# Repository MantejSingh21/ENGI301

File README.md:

# <h1> ENGI301 Project 1 + 2 
# <h1> Bubba the Spider Robot

This is the repository that contains information on building Bubba the spider robot.It contains the code repo.
The full length build and operation instructions are located in the hackster page: 

  https://www.hackster.io/ms146/bubba-the-quadrupedal-spider-robot-7b09ac

 <12/03/21>
This repo also contains the gerber, brd and schem files required to print the custom circuit board. It also contains the bill of materials for all the required part.
   
This is found in project_02/docs.
  
Repository for ENGI301 course work.

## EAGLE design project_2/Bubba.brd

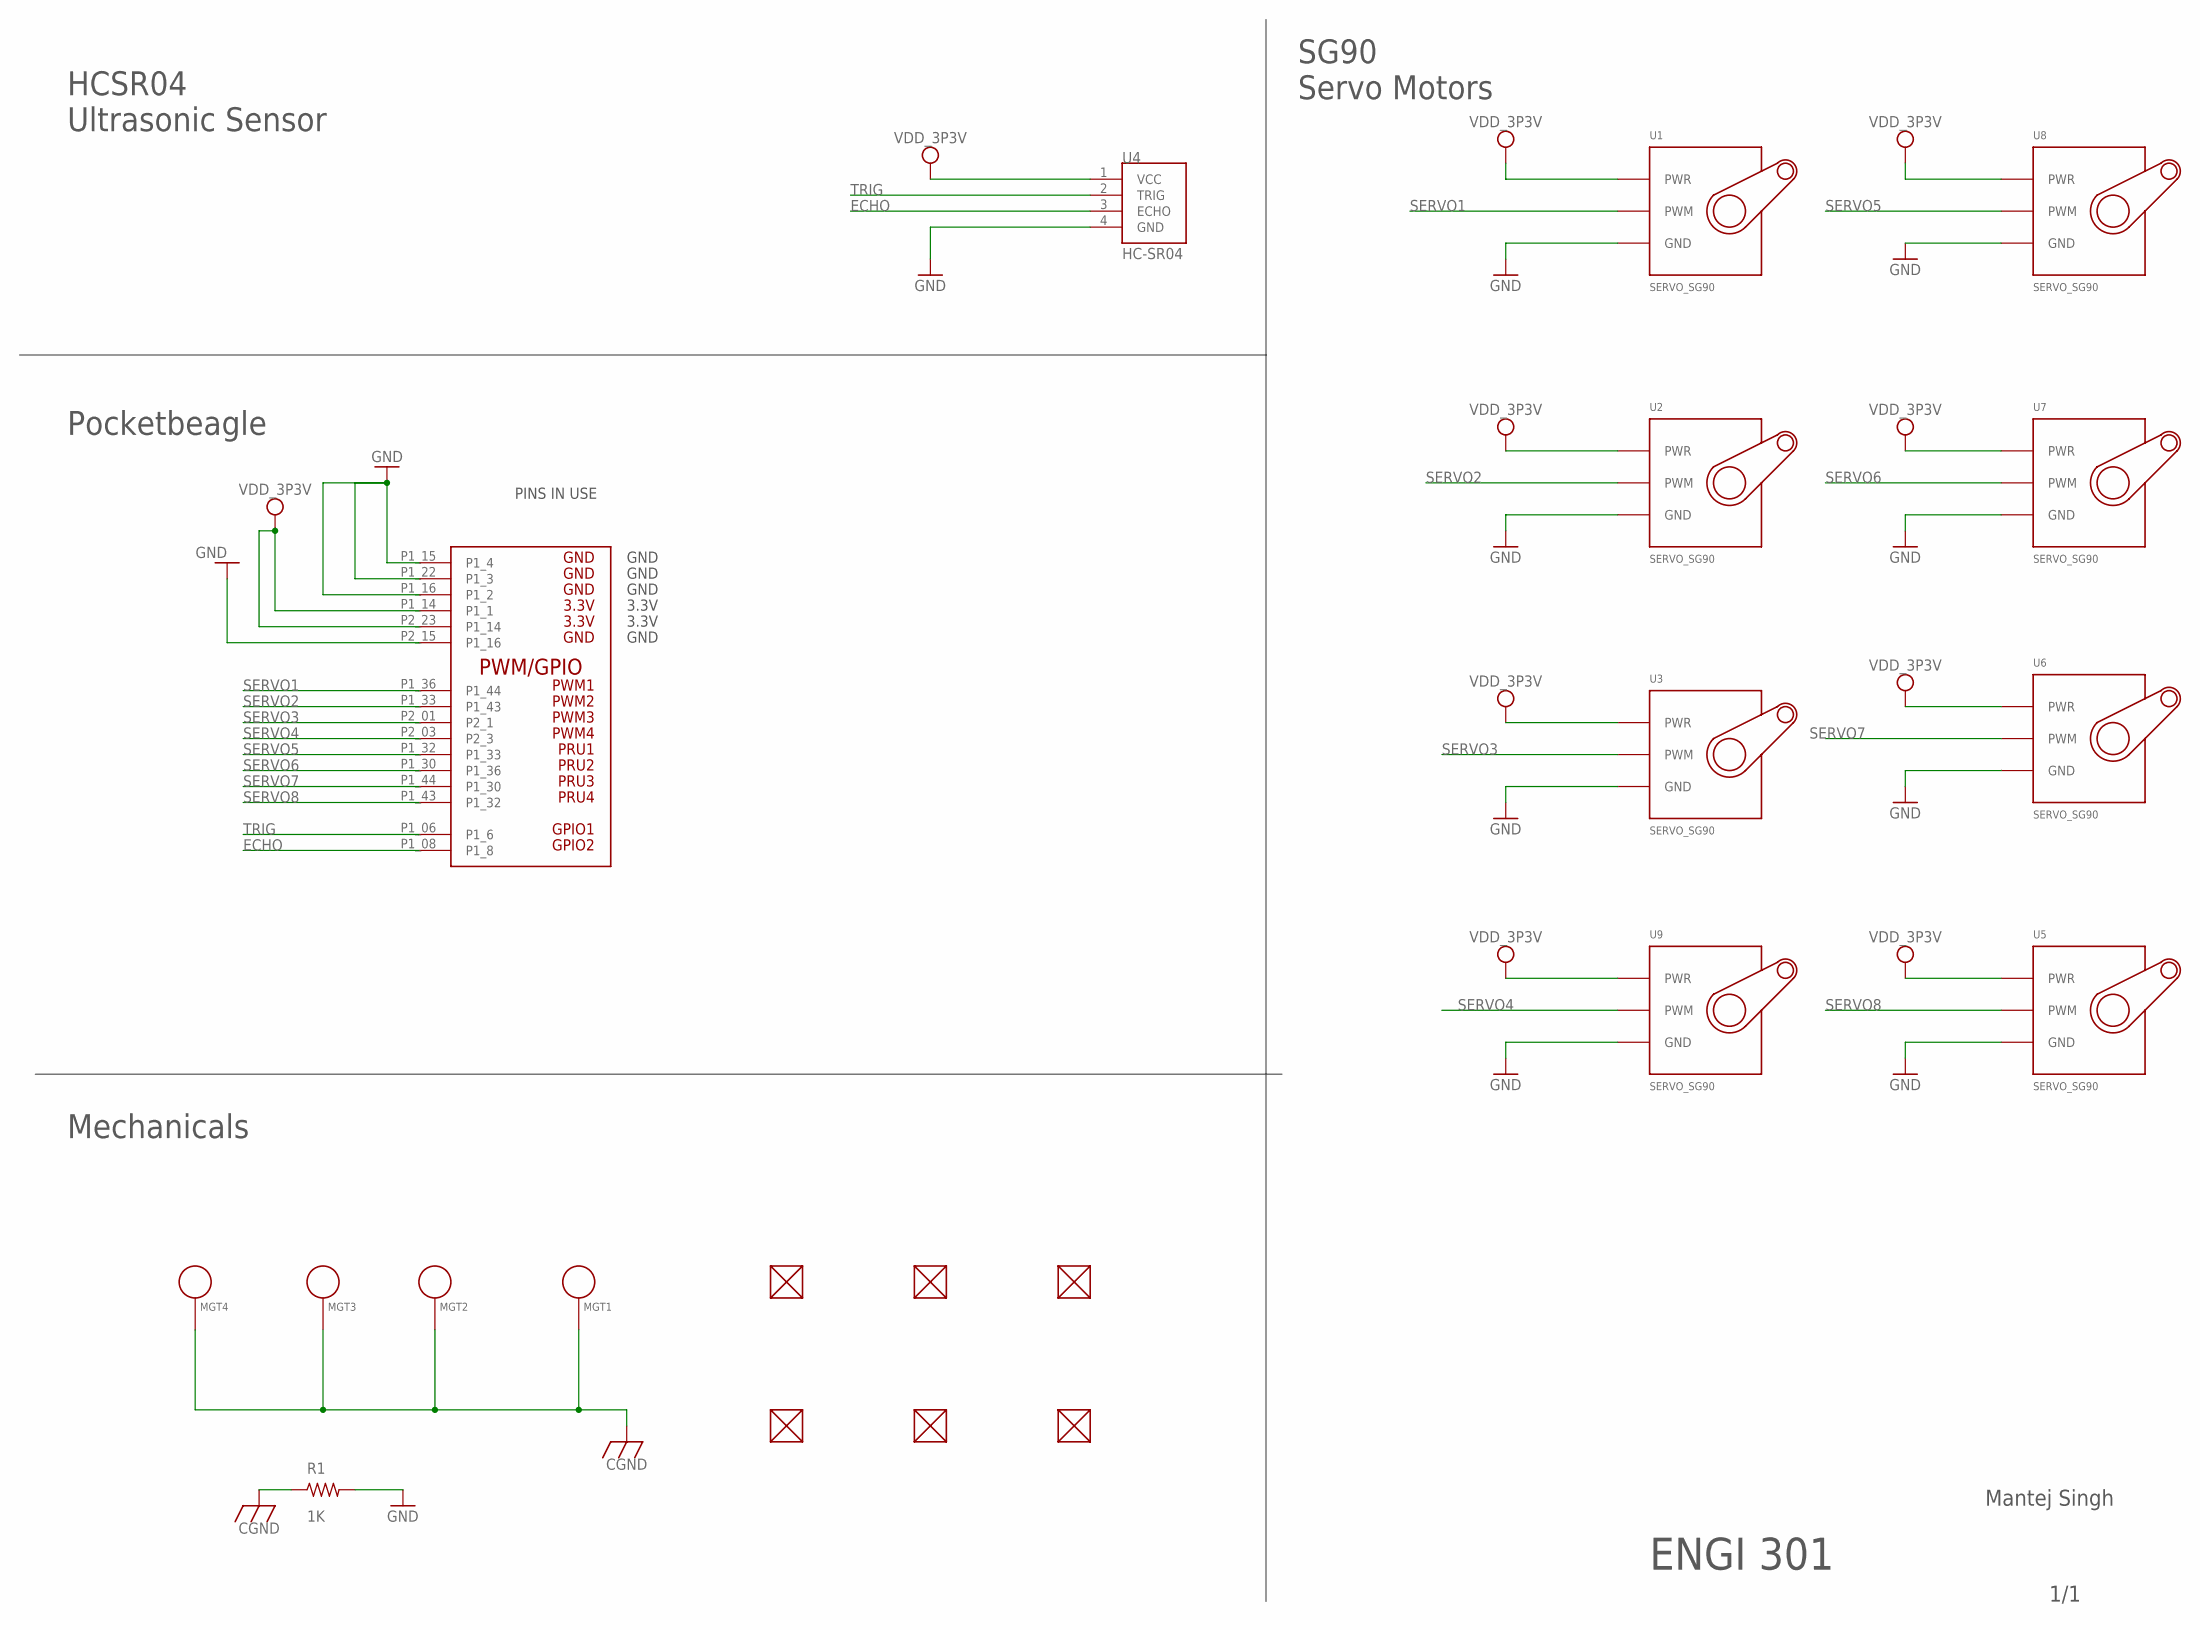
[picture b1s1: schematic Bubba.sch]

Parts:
FUD1, FUD2, FUD3, FUD4, FUD5, FUD6: FIDUCIAL; FIDUCIAL_40MIL
MGT1, MGT2, MGT3, MGT4: MOUNTING_HOLE
R1: 1K; R0805
U1, U2, U3, U5, U6, U7, U8, U9: SERVO_SG90; SERVO-X1
U4: HC-SR04; XCVR_HC-SR04
U$1: POCKETBEAGLE-MANTEJ

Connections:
CGND: MGT1.P$1, MGT2.P$1, MGT3.P$1, MGT4.P$1, R1.1
ECHO: U4.3 (ECHO), U$1.P1_08 (P1_8)
GND: R1.2, U1.GND, U2.GND, U3.GND, U4.4 (GND), U5.GND, U6.GND, U7.GND, U8.GND, U9.GND, U$1.P1_15 (P1_4), U$1.P1_16 (P1_2), U$1.P1_22 (P1_3), U$1.P2_15 (P1_16)
SERVO1: U1.SIG (PWM), U$1.P1_36 (P1_44)
SERVO2: U2.SIG (PWM), U$1.P1_33 (P1_43)
SERVO3: U3.SIG (PWM), U$1.P2_01 (P2_1)
SERVO4: U9.SIG (PWM), U$1.P2_03 (P2_3)
SERVO5: U8.SIG (PWM), U$1.P1_32 (P1_33)
SERVO6: U7.SIG (PWM), U$1.P1_30 (P1_36)
SERVO7: U6.SIG (PWM), U$1.P1_44 (P1_30)
SERVO8: U5.SIG (PWM), U$1.P1_43 (P1_32)
TRIG: U4.2 (TRIG), U$1.P1_06 (P1_6)
VDD_3P3V: U1.PWR, U2.PWR, U3.PWR, U4.1 (VCC), U5.PWR, U6.PWR, U7.PWR, U8.PWR, U9.PWR, U$1.P1_14 (P1_1), U$1.P2_23 (P1_14)

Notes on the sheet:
HCSR04 Ultrasonic Sensor
Pocketbeagle
SG90 Servo Motors
Mechanicals
Mantej Singh
ENGI 301
1/1

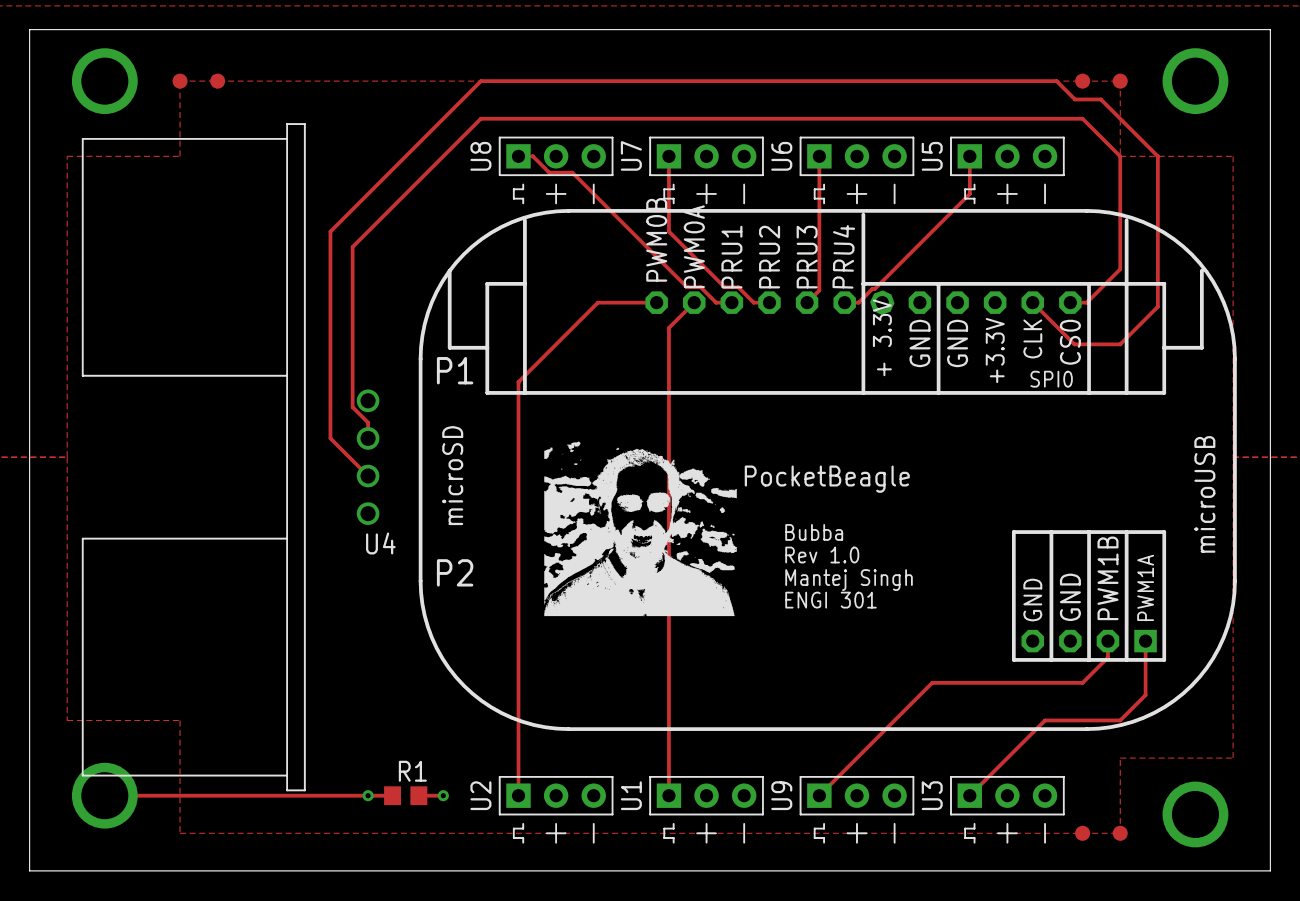
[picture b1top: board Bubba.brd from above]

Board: 4 copper layers, 83.8 x 56.8 mm, 21 parts (0 on the bottom side), 13 nets.

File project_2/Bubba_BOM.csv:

"Qty";"Value";"Device";"Package";"Parts";"Description";"AVAILABILITY";"DESCRIPTION";"MF";"MP";"PACKAGE";"PRICE";
"1";"1K";"R_R0805";"R0805";"R1";"RESISTOR, American symbol";"";"";"";"";"";"";
"6";"FIDUCIAL";"FIDUCIAL";"FIDUCIAL_40MIL";"FUD1, FUD2, FUD3, FUD4, FUD5, FUD6";"";"";"";"";"";"";"";
"1";"HC-SR04";"HC-SR04";"XCVR_HC-SR04";"U4";"Ultrasonic Sensor Module Check prices";"Not in stock";" Multiple Function Sensor Development Tools Ultrasonic Sensor Module ";"SparkFun Electronics";"HC-SR04";"None";"None";
"4";"MOUNTING_HOLE";"MOUNTING_HOLE";"MOUNTING_HOLE";"MGT1, MGT2, MGT3, MGT4";"Chassis Mounting Hole w/GND connection ability";"";"";"";"";"";"";
"1";"POCKETBEAGLE-MANTEJ";"POCKETBEAGLE-MANTEJ";"POCKETBEAGLE-MANTEJ";"U$1";"";"";"";"";"";"";"";
"8";"SERVO_SG90";"SERVO_SG90";"SERVO-X1";"U1, U2, U3, U5, U6, U7, U8, U9";"";"";"";"";"";"";"";

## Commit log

2021-09-12 Updating README.md
2021-09-29 Finished building calculator and led code
2021-10-01 finished simple_calc with python2/3 support
2021-10-08 Added project 1 docs
2021-10-08 Added recursive function to control legs of robot
2021-10-09 Added code for movement
2021-11-08 Pushed changes and completed project 1
2021-11-08 Completed Project 1
2021-11-08 Finished project 1
2021-11-08 Added project_o2 files
2021-11-15 Added proj 2 proposal
2021-11-15 Added proj 2 docs
2021-12-02 Added all required schematic files
